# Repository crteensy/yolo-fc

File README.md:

# Yolo FC, STM32F7, 2-6S
This FC has been test flown with a 3" quad, and it flew well. flight logs of the maiden flight are in /logs

- Main MCU: STM32F745
- IMU: ICM-20602
- Flash: 8MB
- Baro: BMP280
- OSD: '7456
- GNSS: Integrated GPS module (uBlox ZOE-M8Q) with u.Fl connector and experimental support for active antennas
- 4 ESCs:
  - EFM8BB21 / bluejay
  - Calculated current rating of 20A continuous 30A burst (depending on the airflow cooling situation)
- Current sensor: INA186 with 0m5 shunt - subjectively some of the best current measurements we have seen on any FC
- 4 multi purpose expansion connectors:
  - each with its own UART
  - shared I2C bus
  - 5V, 3V3 and GND
  - a multi-purpose pin for analog RSSI, Buzzer, LEDs, etc.
- One video expansion connector:
  - Camera in and VTx out
  - UART
  - 2 multi-purpose pins
  - switchable 5V (*)
- size: 30 x 25.2 mm

The expansion connectors can be used with very simple or more complex plug-ins for
- Rx of your choice
- Magnetometer
- Buzzer
- LED strip
- dual camera switching on the OSD connector
- even additional plugin ESCs for hexa- and octocopters are possible

*) The OSD connector has a 5V output that is only ON when USB is not plugged in. This protects your USB port from power hungry VTx'es that might overload the port. However, that feature can be disabled with a solder bridge.

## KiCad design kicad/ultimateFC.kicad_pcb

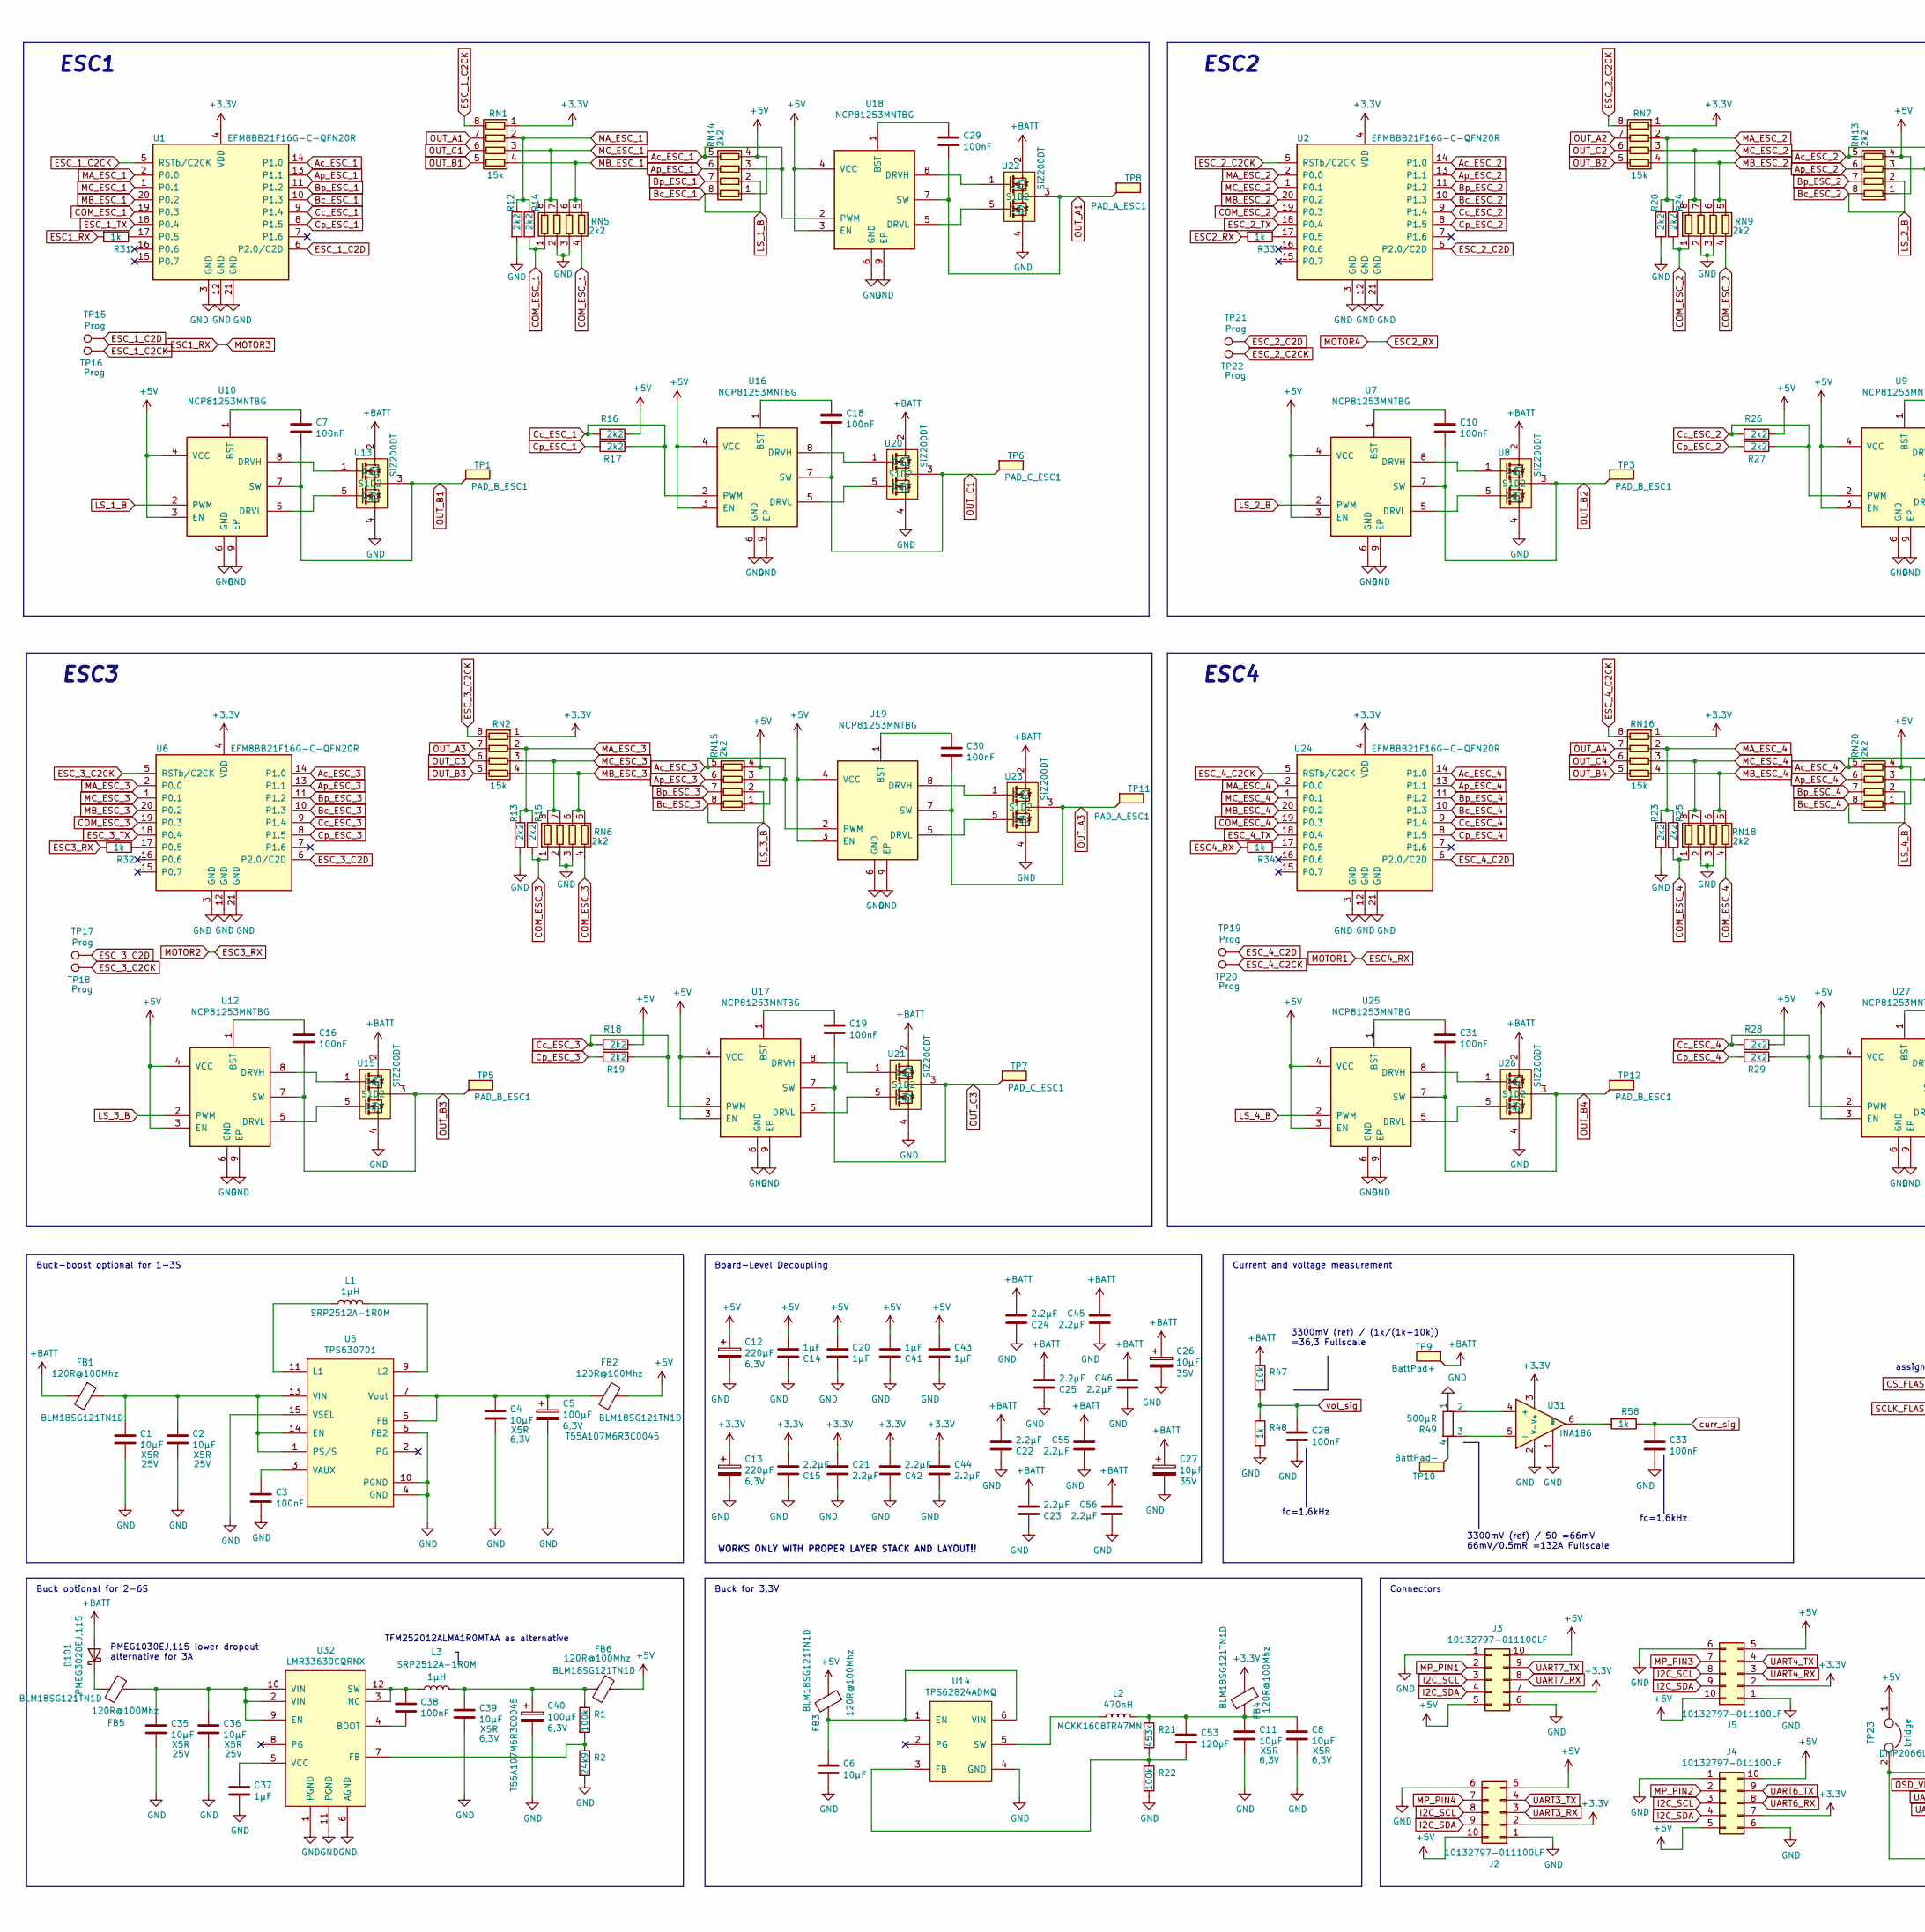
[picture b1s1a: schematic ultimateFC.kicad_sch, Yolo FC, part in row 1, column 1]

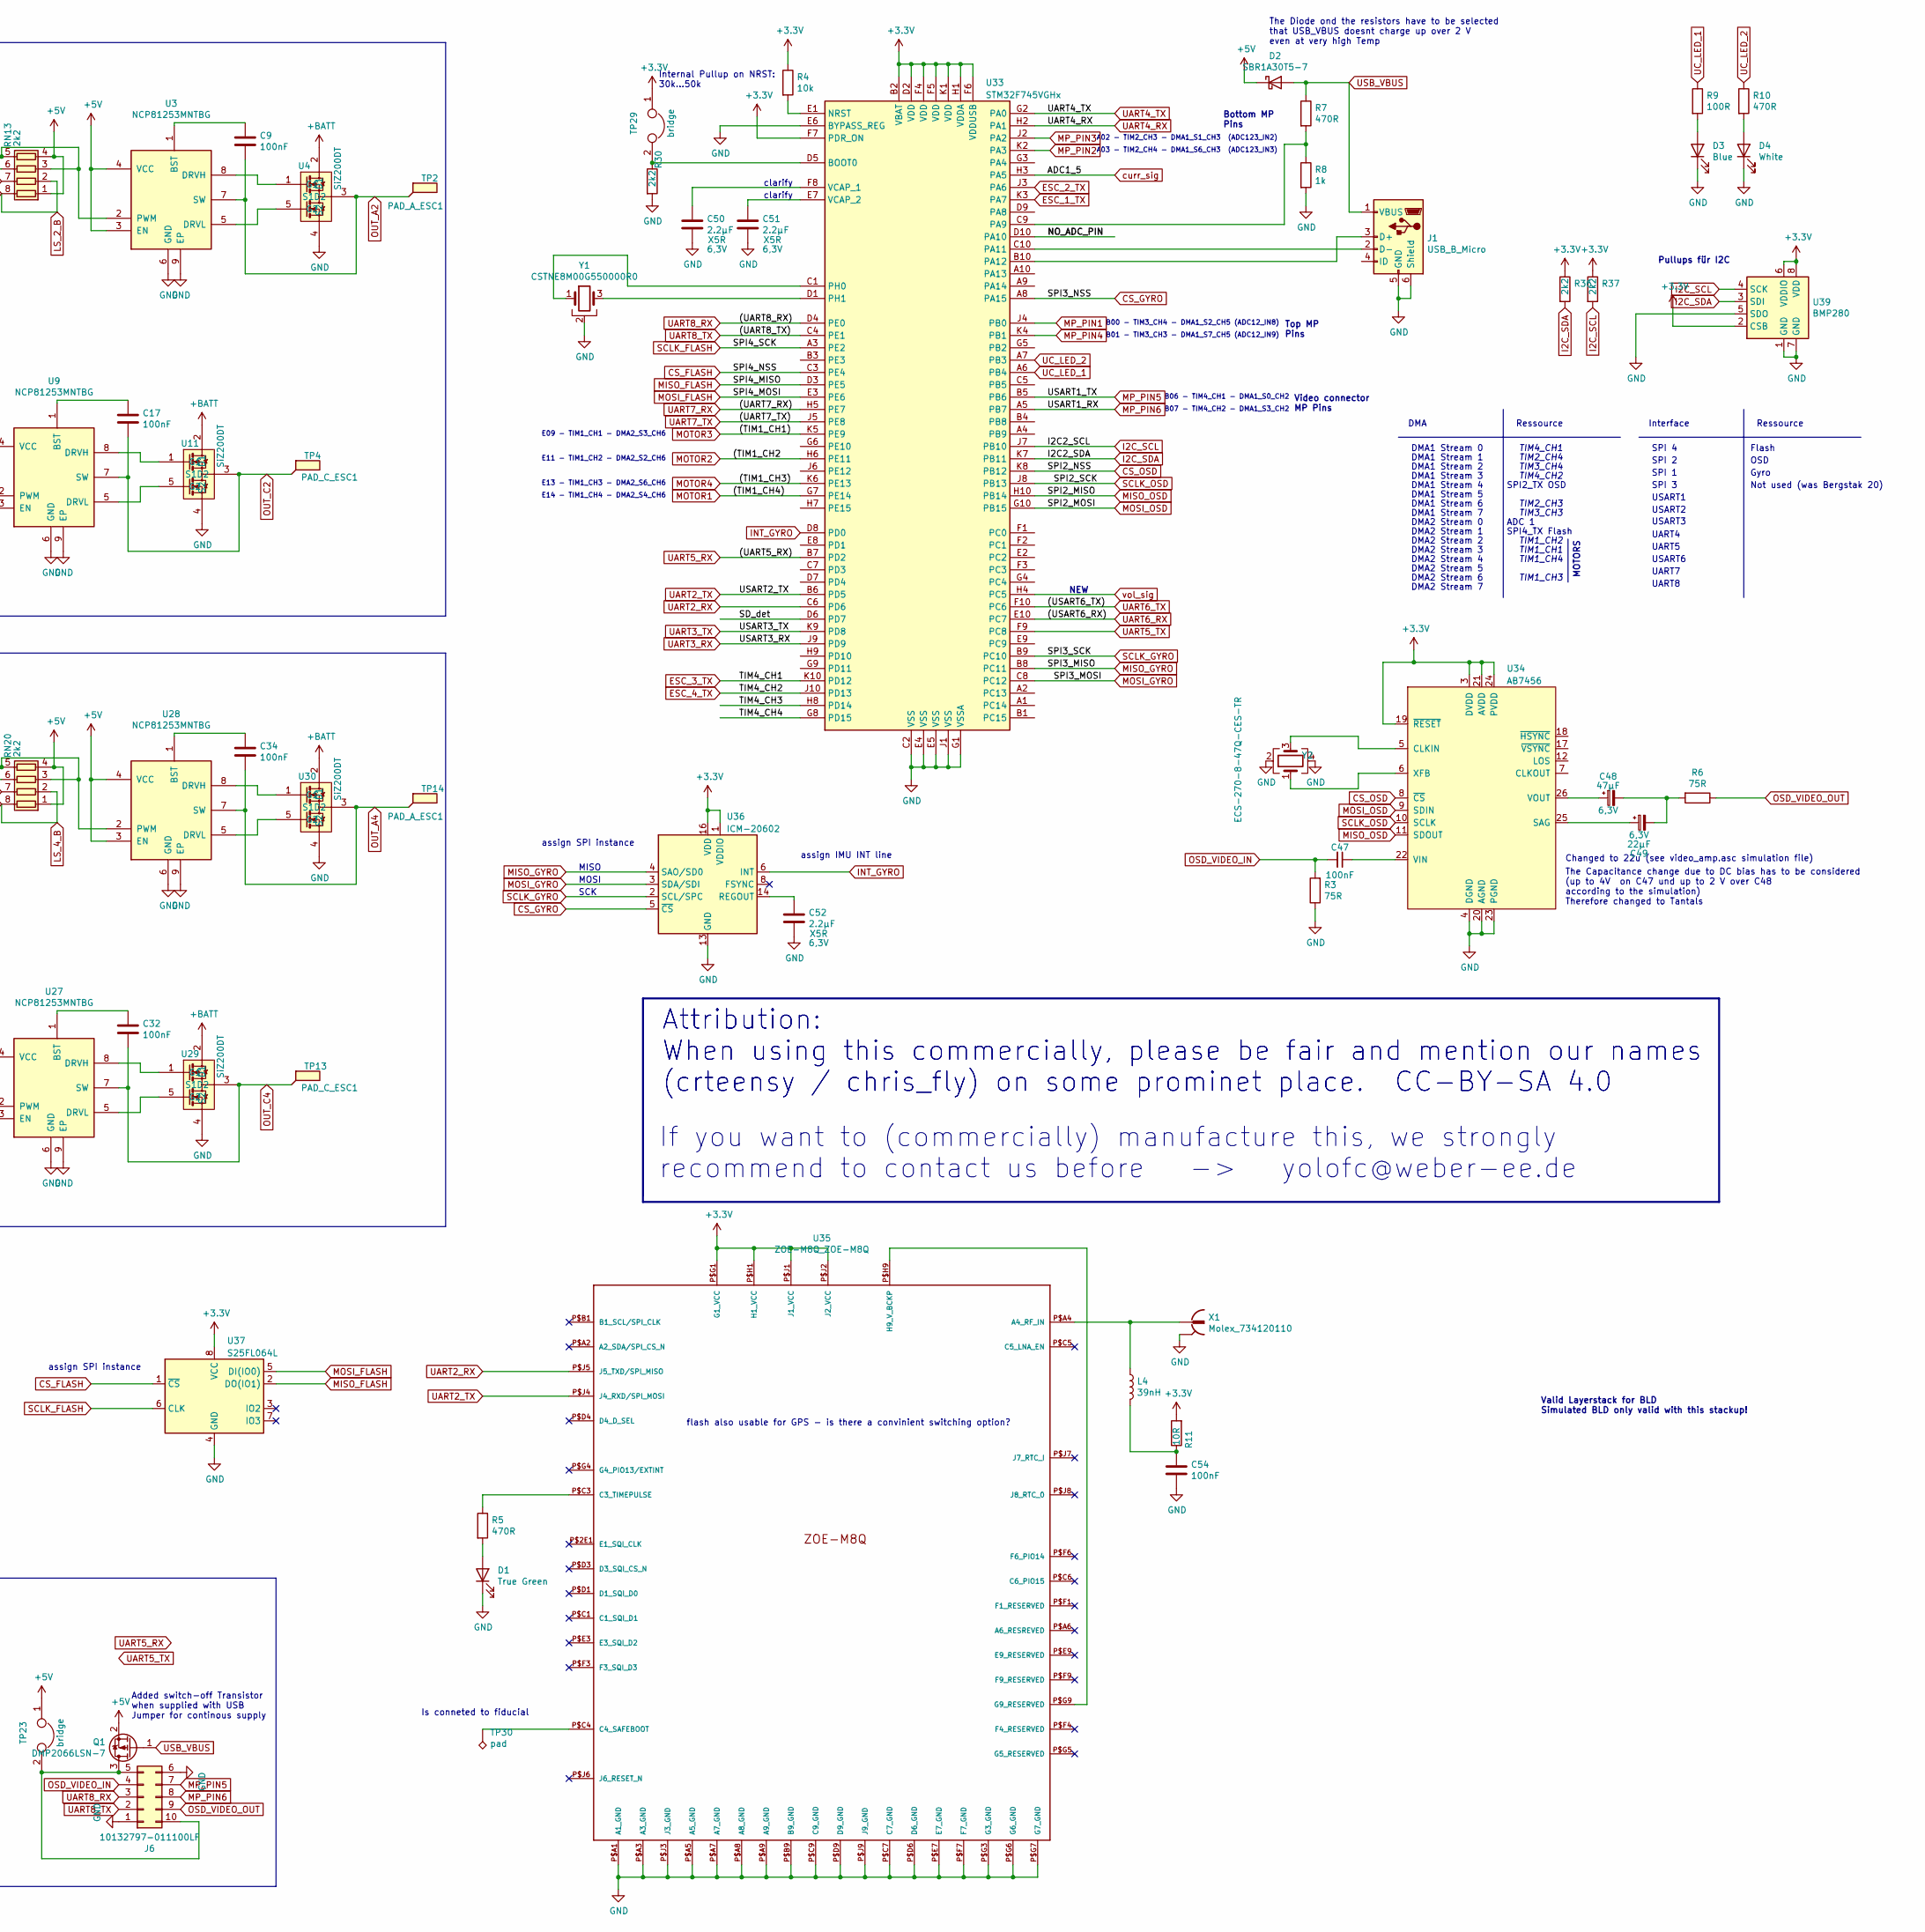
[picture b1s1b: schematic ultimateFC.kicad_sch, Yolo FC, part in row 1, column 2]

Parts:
C1, C2, C35, C36: 10µF; C_1206_3216Metric
C3, C28, C33, C38, C47, C54: 100nF; C_0201_0603Metric_mod
C4, C6, C8, C11, C39: 10µF; C_0603_1608Metric
C5, C40: 100µF; CP_EIA-3216-10_Kemet-I
C7, C9, C10, C16, C17, C18, C19, C29, C30, C31, C32, C34: 100nF; C_0402_1005Metric
C12, C13: 220µF; CP_EIA-3528-15_AVX-H
C14, C20, C41, C43: 1µF; C_AVX_Super_Low_ESL
C15, C21, C42, C44: 2.2µF; C_AVX_Super_Low_ESL
C22, C23, C24, C25, C45, C46, C55, C56: 2.2µF; C_0603_1608Metric
C26, C27: 10µF; CP_EIA-3216-18_Kemet-A
C37: 1µF; C_0402_1005Metric
C48: 47µF; C_0603_1608Metric
C49: 22µF; C_0603_1608Metric
C50, C51, C52: 2.2µF; C_0402_1005Metric
C53: 120pF; C_0201_0603Metric_mod
D1: True Green; LED_0201_0603Metric
D2: SBR1A30T5-7; D_SOD-523
D3: Blue; LED_0201_0603Metric
D4: White; LED_0201_0603Metric
D101: PMEG3020EJ,115; D_SOD-323
FB1, FB2, FB3, FB4, FB5, FB6: 120R@100Mhz; L_0603_1608Metric
J1: USB_B_Micro; USB_Micro-B_Molex_47346-0001
J2, J3, J4, J5, J6: 10132797-011100LF
L1, L3: 1µH; L_Wuerth_MAPI-2506
L2: 470nH; L_0603_1608Metric
L4: 39nH; L_0201_0603Metric
Q1: DMP2066LSN-7; SOT-323_SC-70
R1, R22: 100k; R_0201_0603Metric_mod
R2: 24k9; R_0201_0603Metric_mod
R3, R6: 75R; R_0402_1005Metric
R4: 10k; R_0201_0603Metric_mod
R5, R7, R10: 470R; R_0201_0603Metric_mod
R8, R31, R32, R33, R34, R48, R58: 1k; R_0201_0603Metric_mod
R9: 100R; R_0201_0603Metric_mod
R11: 10R; R_0201_0603Metric_mod
R12, R13, R14, R15, R16, R17, R18, R19, R20, R23, R24, R25, R26, R27, R28, R29, R30, R36, R37: 2k2; R_0201_0603Metric_mod
R21: 453k; R_0201_0603Metric_mod
R47: 10k; R_0402_1005Metric
R49: 500µR; R_Shunt_Vishay_WSKW0612
RN1, RN2, RN7, RN16: 15k; R_Array_Convex_4x0402
RN5, RN6, RN9, RN13, RN14, RN15, RN18, RN20: 2k2; EXB18V_0201x4
TP1, TP3, TP5, TP12: PAD_B_ESC1; esc_pad
TP2, TP8, TP11, TP14: PAD_A_ESC1; esc_pad
TP4, TP6, TP7, TP13: PAD_C_ESC1; esc_pad
TP9: BattPad+; batt_conn_oval
TP10: BattPad-; batt_conn_oval
TP15, TP16, TP17, TP18, TP19, TP20, TP21, TP22: Prog; programm_pad_esc
TP23, TP29: bridge; solderbridge_tiny
TP30: pad; TestPoint_Pad_1.0x1.0mm
U1, U2, U6, U24: EFM8BB21F16G-C-QFN20R; SiliconLabs_QFN-20-1EP_3x3mm_P0.5mm
U3, U7, U9, U10, U12, U16, U17, U18, U19, U25, U27, U28: NCP81253MNTBG; DFN-8-1EP_2x2mm_P0.5mm_EP0.9x1.3mm
U4, U8, U11, U13, U15, U20, U21, U22, U23, U26, U29, U30: SiZ200DT; PowerPAIR3.3x3.3
U5: TPS630701; TEXAS_15-VQFN-HR
U14: TPS62824ADMQ; VSON_HR6
U31: INA186; SOT-363_SC-70-6
U32: LMR33630CQRNX; Texas_RNX0012B
U33: STM32F745VGHx; TFBGA-100_8x8mm_Layout10x10_P0.8mm
U34: AB7456; TSSOP-28_4.4x9.7mm_P0.65mm
U35: ZOE-M8Q_ZOE-M8Q; ZOE-M8
U36: ICM-20602; LGA-16_3x3mm_P0.5mm_LayoutBorder3x5y
U37: S25FL064L; WSON-8_4x4mm_P0.8mm
U39: BMP280; Bosch_LGA-8_2x2.5mm_P0.65mm_ClockwisePinNumbering
X1: Molex_734120110
Y1: CSTNE8M00G550000R0; Resonator_SMD_muRata_CSTxExxV-3Pin_3.0x1.1mm
Y2: ECS-270-8-47Q-CES-TR; ECX-1247Q

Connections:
+3V3: C13.1, C15.2, C21.1, C42.2, C44.1, FB4.1, J2.2, J3.7, J4.7, J5.2, R4.1, R11.2, R36.1, R37.1, RN1.1 (R1.1), RN2.1 (R1.1), RN7.1 (R1.1), RN16.1 (R1.1), TP29.1, U1.4 (VDD), U2.4 (VDD), U6.4 (VDD), U24.4 (VDD), U31.3 (V+), U33.B2 (VBAT), U33.D2 (VDD), U33.F4 (VDD), U33.F5 (VDD), U33.F6 (VDDUSB), U33.F7 (PDR_ON), U33.H1 (VDDA), U33.K1 (VDD), U34.3 (DVDD), U34.19 (~RESET), U34.21 (AVDD), U34.24 (PVDD), U35.P$G1 (G1_VCC), U35.P$H1 (H1_VCC), U35.P$J1 (J1_VCC), U35.P$J2 (J2_VCC), U36.1 (VDDIO), U36.16 (VDD), U37.8 (VCC), U39.2 (CSB), U39.6 (VDDIO), U39.8 (VDD)
+5V: C12.1, C14.2, C20.1, C41.2, C43.1, D2.1 (K), FB2.1, FB3.1, FB6.1, J2.5, J2.10, J3.5, J3.10, J4.5, J4.10, J5.5, J5.10, Q1.2 (S), R16.1, R18.1, R26.1, R28.1, RN13.1 (R1.1), RN13.4 (R4.1), RN14.1 (R1.1), RN14.4 (R4.1), RN15.1 (R1.1), RN15.4 (R4.1), RN20.1 (R1.1), RN20.4 (R4.1), TP23.1, U3.3 (EN), U3.4 (VCC), U7.3 (EN), U7.4 (VCC), U9.3 (EN), U9.4 (VCC), U10.3 (EN), U10.4 (VCC), U12.3 (EN), U12.4 (VCC), U16.3 (EN), U16.4 (VCC), U17.3 (EN), U17.4 (VCC), U18.3 (EN), U18.4 (VCC), U19.3 (EN), U19.4 (VCC), U25.3 (EN), U25.4 (VCC), U27.3 (EN), U27.4 (VCC), U28.3 (EN), U28.4 (VCC)
+BATT: C22.2, C23.2, C24.2, C25.2, C26.1, C27.1, C45.1, C46.1, C55.1, C56.1, D101.2 (A), FB1.2, R47.1, TP9.1, U4.2 (D1), U8.2 (D1), U11.2 (D1), U13.2 (D1), U15.2 (D1), U20.2 (D1), U21.2 (D1), U22.2 (D1), U23.2 (D1), U26.2 (D1), U29.2 (D1), U30.2 (D1)
/NO_ADC_PIN: U33.D10 (PA10)
/SD_det: U33.D6 (PD7)
/TIM4_CH3: U33.H8 (PD14)
/TIM4_CH4: U33.G8 (PD15)
Ac_ESC_1: RN14.3 (R3.1), RN14.5 (R4.2), U1.14 (P1.0), U18.2 (PWM)
Ac_ESC_2: RN13.3 (R3.1), RN13.5 (R4.2), U2.14 (P1.0), U3.2 (PWM)
Ac_ESC_3: RN15.3 (R3.1), RN15.5 (R4.2), U6.14 (P1.0), U19.2 (PWM)
Ac_ESC_4: RN20.3 (R3.1), RN20.5 (R4.2), U24.14 (P1.0), U28.2 (PWM)
Ap_ESC_1: RN14.6 (R3.2), U1.13 (P1.1)
Ap_ESC_2: RN13.6 (R3.2), U2.13 (P1.1)
Ap_ESC_3: RN15.6 (R3.2), U6.13 (P1.1)
Ap_ESC_4: RN20.6 (R3.2), U24.13 (P1.1)
Bc_ESC_1: RN14.2 (R2.1), RN14.8 (R1.2), U1.10 (P1.3), U10.2 (PWM)
Bc_ESC_2: RN13.2 (R2.1), RN13.8 (R1.2), U2.10 (P1.3), U7.2 (PWM)
Bc_ESC_3: RN15.2 (R2.1), RN15.8 (R1.2), U6.10 (P1.3), U12.2 (PWM)
Bc_ESC_4: RN20.2 (R2.1), RN20.8 (R1.2), U24.10 (P1.3), U25.2 (PWM)
Bp_ESC_1: RN14.7 (R2.2), U1.11 (P1.2)
Bp_ESC_2: RN13.7 (R2.2), U2.11 (P1.2)
Bp_ESC_3: RN15.7 (R2.2), U6.11 (P1.2)
Bp_ESC_4: RN20.7 (R2.2), U24.11 (P1.2)
COM_ESC_1: R14.2, RN5.1 (R1.1), RN5.4 (R4.1), U1.19 (P0.3)
COM_ESC_2: R24.2, RN9.1 (R1.1), RN9.4 (R4.1), U2.19 (P0.3)
COM_ESC_3: R15.2, RN6.1 (R1.1), RN6.4 (R4.1), U6.19 (P0.3)
COM_ESC_4: R25.2, RN18.1 (R1.1), RN18.4 (R4.1), U24.19 (P0.3)
CS_FLASH: U33.C3 (PE4), U37.1 (~CS)
CS_GYRO: U33.A8 (PA15), U36.5 (~CS)
CS_OSD: U33.K8 (PB12), U34.8 (~CS)
Cc_ESC_1: R16.2, R17.1, U1.9 (P1.4), U16.2 (PWM)
Cc_ESC_2: R26.2, R27.1, U2.9 (P1.4), U9.2 (PWM)
Cc_ESC_3: R18.2, R19.1, U6.9 (P1.4), U17.2 (PWM)
Cc_ESC_4: R28.2, R29.1, U24.9 (P1.4), U27.2 (PWM)
Cp_ESC_1: R17.2, U1.8 (P1.5)
Cp_ESC_2: R27.2, U2.8 (P1.5)
Cp_ESC_3: R19.2, U6.8 (P1.5)
Cp_ESC_4: R29.2, U24.8 (P1.5)
ESC1_RX: R31.2, U33.K5 (PE9)
ESC2_RX: R33.2, U33.K6 (PE13)
ESC3_RX: R32.2, U33.H6 (PE11)
ESC4_RX: R34.2, U33.G7 (PE14)
ESC_1_C2CK: RN1.8 (R1.2), TP16.1, U1.5 (RSTb/C2CK)
ESC_1_C2D: TP15.1, U1.6 (P2.0/C2D)
ESC_1_TX: U1.18 (P0.4), U33.K3 (PA7)
ESC_2_C2CK: RN7.8 (R1.2), TP22.1, U2.5 (RSTb/C2CK)
ESC_2_C2D: TP21.1, U2.6 (P2.0/C2D)
ESC_2_TX: U2.18 (P0.4), U33.J3 (PA6)
ESC_3_C2CK: RN2.8 (R1.2), TP18.1, U6.5 (RSTb/C2CK)
ESC_3_C2D: TP17.1, U6.6 (P2.0/C2D)
ESC_3_TX: U6.18 (P0.4), U33.K10 (PD12)
ESC_4_C2CK: RN16.8 (R1.2), TP20.1, U24.5 (RSTb/C2CK)
ESC_4_C2D: TP19.1, U24.6 (P2.0/C2D)
ESC_4_TX: U24.18 (P0.4), U33.J10 (PD13)
GND: C1.2, C2.2, C3.2, C4.2, C5.2, C6.2, C8.2, C11.2, C12.2, C13.2, C14.1, C15.1, C20.2, C21.2, C22.1, C23.1, C24.1, C25.1, C26.2, C27.2, C28.2, C33.2, C35.2, C36.2, C37.2, C39.2, C40.2, C41.1, C42.1, C43.2, C44.2, C45.2, C46.2, C50.2, C51.2, C52.2, C54.2, C55.2, C56.2, D1.1 (K), D3.1 (K), D4.1 (K), J1.5 (GND), J1.6 (Shield), J2.1, J2.6, J3.1, J3.6, J4.1, J4.6, J5.1, J5.6, J6.1, J6.6, R2.2, R3.1, R8.2, R12.2, R13.2, R20.2, R22.2, R23.2, R30.2, R48.2, R49.1, RN5.2 (R2.1), RN5.3 (R3.1), RN6.2 (R2.1), RN6.3 (R3.1), RN9.2 (R2.1), RN9.3 (R3.1), RN18.2 (R2.1), RN18.3 (R3.1), U1.3 (GND), U1.12 (GND), U1.21 (GND), U2.3 (GND), U2.12 (GND), U2.21 (GND), U3.6 (GND), U3.9 (EP), U4.4 (S2), U5.4 (GND), U5.6 (FB2), U5.10 (PGND), U5.15 (VSEL), U6.3 (GND), U6.12 (GND), U6.21 (GND), U7.6 (GND), U7.9 (EP), U8.4 (S2), U9.6 (GND), U9.9 (EP), U10.6 (GND), U10.9 (EP), U11.4 (S2), U12.6 (GND), U12.9 (EP), U13.4 (S2), U14.4 (GND), U15.4 (S2), U16.6 (GND)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
I2C_SCL: J2.8, J3.3, J4.3, J5.8, R37.2, U33.J7 (PB10), U39.4 (SCK)
I2C_SDA: J2.9, J3.4, J4.4, J5.9, R36.2, U33.K7 (PB11), U39.3 (SDI)
INT_GYRO: U33.D8 (PD0), U36.6 (INT)
MA_ESC_1: R12.1, R14.1, RN1.2 (R2.1), U1.2 (P0.0)
MA_ESC_2: R20.1, R24.1, RN7.2 (R2.1), U2.2 (P0.0)
MA_ESC_3: R13.1, R15.1, RN2.2 (R2.1), U6.2 (P0.0)
MA_ESC_4: R23.1, R25.1, RN16.2 (R2.1), U24.2 (P0.0)
MB_ESC_1: RN1.4 (R4.1), RN5.5 (R4.2), RN5.6 (R3.2), U1.20 (P0.2)
MB_ESC_2: RN7.4 (R4.1), RN9.5 (R4.2), RN9.6 (R3.2), U2.20 (P0.2)
MB_ESC_3: RN2.4 (R4.1), RN6.5 (R4.2), RN6.6 (R3.2), U6.20 (P0.2)
MB_ESC_4: RN16.4 (R4.1), RN18.5 (R4.2), RN18.6 (R3.2), U24.20 (P0.2)
MC_ESC_1: RN1.3 (R3.1), RN5.7 (R2.2), RN5.8 (R1.2), U1.1 (P0.1)
MC_ESC_2: RN7.3 (R3.1), RN9.7 (R2.2), RN9.8 (R1.2), U2.1 (P0.1)
MC_ESC_3: RN2.3 (R3.1), RN6.7 (R2.2), RN6.8 (R1.2), U6.1 (P0.1)
MC_ESC_4: RN16.3 (R3.1), RN18.7 (R2.2), RN18.8 (R1.2), U24.1 (P0.1)
MISO_FLASH: U33.D3 (PE5), U37.2 (DO(IO1))
MISO_GYRO: U33.B8 (PC11), U36.4 (SAO/SD0)
MISO_OSD: U33.H10 (PB14), U34.11 (SDOUT)
MOSI_FLASH: U33.E3 (PE6), U37.5 (DI(IO0))
MOSI_GYRO: U33.C8 (PC12), U36.3 (SDA/SDI)
MOSI_OSD: U33.G10 (PB15), U34.9 (SDIN)
MP_PIN1: J3.2, U33.J4 (PB0)
MP_PIN2: J4.2, U33.K2 (PA3)
MP_PIN3: J5.7, U33.J2 (PA2)
MP_PIN4: J2.7, U33.K4 (PB1)
MP_PIN5: J6.7, U33.B5 (PB6)
MP_PIN6: J6.8, U33.A5 (PB7)
unnamed: C1.1, C2.1, FB1.1, U5.1 (PS/S), U5.13 (VIN), U5.14 (EN)
unnamed: C3.1, U5.3 (VAUX)
unnamed: C4.1, C5.1, FB2.2, U5.5 (FB), U5.7 (Vout)
unnamed: C6.1, FB3.2, U14.1 (EN), U14.6 (VIN)
unnamed: C7.1, U10.1 (BST)
unnamed: C9.1, U3.1 (BST)
unnamed: C10.1, U7.1 (BST)
unnamed: C8.1, C11.1, C53.1, FB4.2, L2.2, R21.1
unnamed: C16.1, U12.1 (BST)
unnamed: C17.1, U9.1 (BST)
unnamed: C18.1, U16.1 (BST)
unnamed: C19.1, U17.1 (BST)
unnamed: C29.1, U18.1 (BST)
unnamed: C30.1, U19.1 (BST)
unnamed: C31.1, U25.1 (BST)
unnamed: C32.1, U27.1 (BST)
unnamed: C34.1, U28.1 (BST)
unnamed: C35.1, C36.1, FB5.2, U32.2 (VIN), U32.9 (EN), U32.10 (VIN)
unnamed: C37.1, U32.5 (VCC)
unnamed: C38.1, L3.1, U32.3 (NC), U32.12 (SW)
unnamed: C38.2, U32.4 (BOOT)
unnamed: C39.1, C40.1, FB6.2, L3.2, R1.1
unnamed: C47.1, U34.22 (VIN)
unnamed: C48.1, U34.26 (VOUT)
unnamed: C48.2, C49.2, R6.2
unnamed: C49.1, U34.25 (SAG)
unnamed: C50.1, U33.F8 (VCAP_1)
unnamed: C51.1, U33.E7 (VCAP_2)
unnamed: C52.1, U36.14 (REGOUT)
unnamed: C53.2, R21.2, R22.1, U14.3 (FB)
unnamed: C54.1, L4.2, R11.1
unnamed: D1.2 (A), R5.2
unnamed: D3.2 (A), R9.2
unnamed: D4.2 (A), R10.2
unnamed: D101.1 (K), FB5.1
unnamed: J1.2 (D-), U33.C10 (PA11)
unnamed: J1.3 (D+), U33.B10 (PA12)
unnamed: J6.5, J6.10, Q1.3 (D), TP23.2
unnamed: L1.1, U5.11 (L1)
unnamed: L1.2, U5.9 (L2)
unnamed: L2.1, U14.5 (SW)
unnamed: L4.1, U35.P$A4 (A4_RF_IN), X1.1
unnamed: R1.2, R2.1, U32.7 (FB)
unnamed: R4.2, U33.E1 (NRST)
unnamed: R5.1, U35.P$C3 (C3_TIMEPULSE)
unnamed: R7.2, R8.1, U33.C9 (PA9)
unnamed: R30.1, TP29.2, U33.D5 (BOOT0)
unnamed: R31.1, U1.17 (P0.5)
unnamed: R32.1, U6.17 (P0.5)
unnamed: R33.1, U2.17 (P0.5)
unnamed: R34.1, U24.17 (P0.5)
unnamed: R49.2, U31.4 (+)
unnamed: R49.3, U31.5 (-)
unnamed: R49.4, TP10.1
unnamed: R58.2, U31.6
unnamed: TP30.1, U35.P$C4 (C4_SAFEBOOT)
unnamed: U3.5 (DRVL), U4.5 (G2)
unnamed: U3.8 (DRVH), U4.1 (G1)
unnamed: U7.5 (DRVL), U8.5 (G2)
unnamed: U7.8 (DRVH), U8.1 (G1)
unnamed: U10.5 (DRVL), U13.5 (G2)
unnamed: U10.8 (DRVH), U13.1 (G1)
unnamed: U9.8 (DRVH), U11.1 (G1)
unnamed: U9.5 (DRVL), U11.5 (G2)
unnamed: U12.5 (DRVL), U15.5 (G2)
unnamed: U12.8 (DRVH), U15.1 (G1)
unnamed: U16.5 (DRVL), U20.5 (G2)
unnamed: U16.8 (DRVH), U20.1 (G1)
unnamed: U17.5 (DRVL), U21.5 (G2)
unnamed: U17.8 (DRVH), U21.1 (G1)
unnamed: U18.5 (DRVL), U22.5 (G2)
unnamed: U18.8 (DRVH), U22.1 (G1)
unnamed: U19.5 (DRVL), U23.5 (G2)
unnamed: U19.8 (DRVH), U23.1 (G1)
unnamed: U25.5 (DRVL), U26.5 (G2)
unnamed: U25.8 (DRVH), U26.1 (G1)
unnamed: U27.5 (DRVL), U29.5 (G2)
unnamed: U27.8 (DRVH), U29.1 (G1)
unnamed: U28.5 (DRVL), U30.5 (G2)
unnamed: U28.8 (DRVH), U30.1 (G1)
unnamed: U33.C1 (PH0), Y1.1
unnamed: U33.D1 (PH1), Y1.3
unnamed: U34.5 (CLKIN), Y2.3
unnamed: U34.6 (XFB), Y2.1
unnamed: U35.P$G9 (G9_RESERVED), U35.P$H9 (H9_V_BCKP)
OSD_VIDEO_IN: C47.2, J6.4, R3.2
OSD_VIDEO_OUT: J6.9, R6.1
OUT_A1: C29.2, RN1.7 (R2.2), TP8.1, U18.7 (SW), U22.3 (S1D2)
OUT_A2: C9.2, RN7.7 (R2.2), TP2.1, U3.7 (SW), U4.3 (S1D2)
OUT_A3: C30.2, RN2.7 (R2.2), TP11.1, U19.7 (SW), U23.3 (S1D2)
OUT_A4: C34.2, RN16.7 (R2.2), TP14.1, U28.7 (SW), U30.3 (S1D2)
OUT_B1: C7.2, RN1.5 (R4.2), TP1.1, U10.7 (SW), U13.3 (S1D2)
OUT_B2: C10.2, RN7.5 (R4.2), TP3.1, U7.7 (SW), U8.3 (S1D2)
OUT_B3: C16.2, RN2.5 (R4.2), TP5.1, U12.7 (SW), U15.3 (S1D2)
OUT_B4: C31.2, RN16.5 (R4.2), TP12.1, U25.7 (SW), U26.3 (S1D2)
OUT_C1: C18.2, RN1.6 (R3.2), TP6.1, U16.7 (SW), U20.3 (S1D2)
OUT_C2: C17.2, RN7.6 (R3.2), TP4.1, U9.7 (SW), U11.3 (S1D2)
OUT_C3: C19.2, RN2.6 (R3.2), TP7.1, U17.7 (SW), U21.3 (S1D2)
OUT_C4: C32.2, RN16.6 (R3.2), TP13.1, U27.7 (SW), U29.3 (S1D2)
SCLK_FLASH: U33.A3 (PE2), U37.6 (CLK)
SCLK_GYRO: U33.B9 (PC10), U36.2 (SCL/SPC)
SCLK_OSD: U33.J8 (PB13), U34.10 (SCLK)
UART2_RX: U33.C6 (PD6), U35.P$J5 (J5_TXD/SPI_MISO)
UART2_TX: U33.B6 (PD5), U35.P$J4 (J4_RXD/SPI_MOSI)
UART3_RX: J2.3, U33.J9 (PD9)
UART3_TX: J2.4, U33.K9 (PD8)
UART4_RX: J5.3, U33.H2 (PA1)
UART4_TX: J5.4, U33.G2 (PA0)
UART5_RX: U33.B7 (PD2)
UART5_TX: U33.F9 (PC8)
UART6_RX: J4.8, U33.E10 (PC7)
UART6_TX: J4.9, U33.F10 (PC6)
UART7_RX: J3.8, U33.H5 (PE7)
UART7_TX: J3.9, U33.J5 (PE8)
UART8_RX: J6.3, U33.D4 (PE0)
UART8_TX: J6.2, U33.C4 (PE1)
UC_LED_1: R9.1, U33.A6 (PB4)
UC_LED_2: R10.1, U33.A7 (PB3)
USB_VBUS: D2.2 (A), J1.1 (VBUS), Q1.1 (G), R7.1
curr_sig: C33.1, R58.1, U33.H3 (PA5)
vol_sig: C28.1, R47.2, R48.1, U33.H4 (PC5)

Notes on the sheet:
Added switch-off Transistor when supplied with USB Jumper for continous supply
E14 - TIM1_CH4 - DMA2_S4_CH6
The Capacitance change due to DC bias has to be considered (up to 4V on C47 und up to 2 V over C48 according to the simulation) Therefore changed to Tantals
3300mV (ref) / 50 =66mV 66mV/0.5mR =132A Fullscale
Internal Pullup on NRST: 30k...50k
MOTORS
clarify
DMA1 Stream 3
DMA1 Stream 4
Video connector MP Pins
ESC3
UART8
DMA1 Stream 6
SPI 1
TIM4_CH1
E09 - TIM1_CH1 - DMA2_S3_CH6
SCK
TIM1_CH4
DMA2 Stream 2
TIM2_CH4
WORKS ONLY WITH PROPER LAYER STACK AND LAYOUT!!
Bottom MP Pins
ESC2
MOSI
Ressource
assign SPI instance
DMA2 Stream 1
ADC 1
fc=1,6kHz
Gyro
UART4
USART3
B06 - TIM4_CH1 - DMA1_S0_CH2
E11 - TIM1_CH2 - DMA2_S2_CH6
E13 - TIM1_CH3 - DMA2_S6_CH6
DMA2 Stream 6
ESC1
PMEG1030EJ,115 lower dropout alternative for 3A
TIM1_CH1
Buck-boost optional for 1-3S

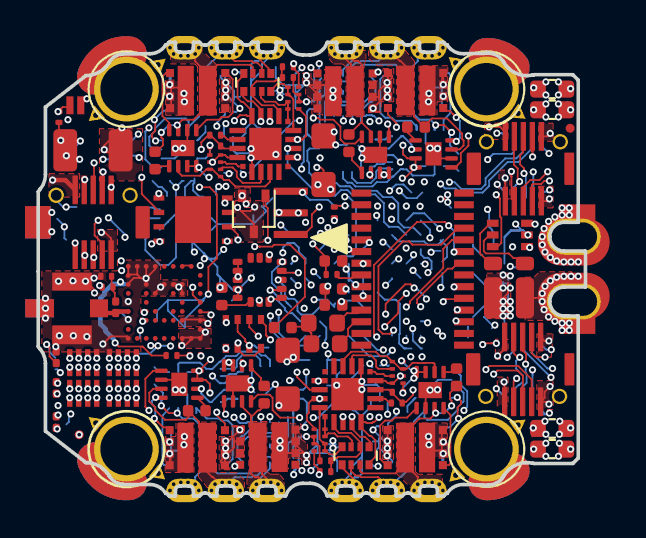
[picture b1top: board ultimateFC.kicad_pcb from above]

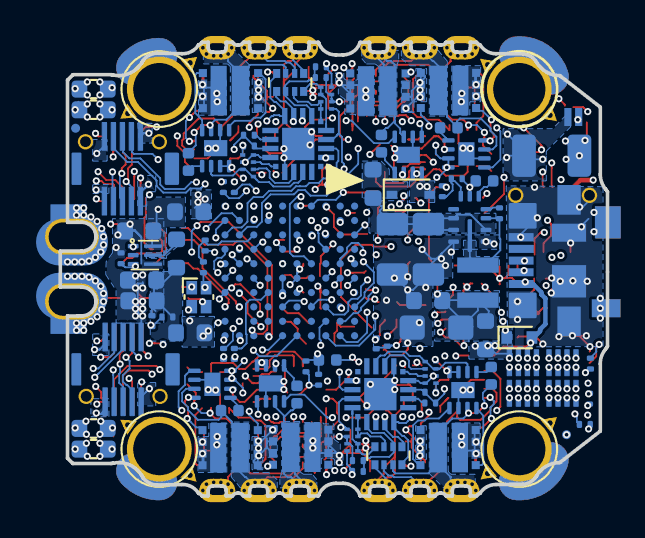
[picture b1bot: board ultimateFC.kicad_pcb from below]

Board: 8 copper layers, 30.4 x 25.2 mm, 186 parts (94 on the bottom side), 191 nets.

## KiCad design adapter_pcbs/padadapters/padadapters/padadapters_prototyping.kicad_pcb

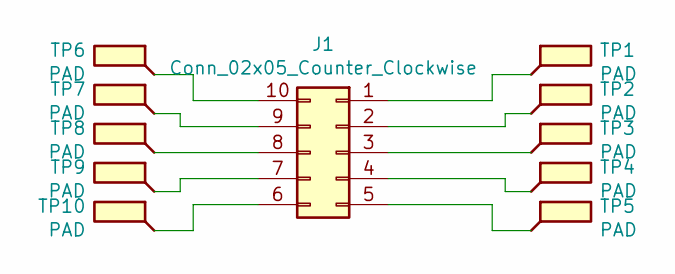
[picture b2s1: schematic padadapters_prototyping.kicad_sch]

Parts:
J1: Conn_02x05_Counter_Clockwise; 10132797-011100LF_mod_small_adapter_pads
TP1, TP2, TP3, TP4, TP5, TP6, TP7, TP8, TP9, TP10: PAD; TestPoint_Pad_1.2x2.5mm

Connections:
unnamed: J1.1, TP1.1
unnamed: J1.2, TP2.1
unnamed: J1.4, TP4.1
unnamed: J1.5, TP5.1
unnamed: J1.6, TP10.1
unnamed: J1.7, TP9.1
unnamed: J1.8, TP8.1
unnamed: J1.9, TP7.1
unnamed: J1.10, TP6.1
unnamed: J1.3, TP3.1

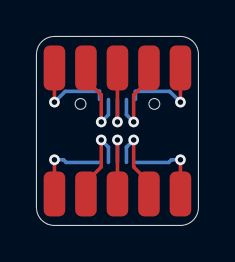
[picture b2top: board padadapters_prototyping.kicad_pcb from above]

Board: 2 copper layers, 9.0 x 10.5 mm, 11 parts (1 on the bottom side), 10 nets.

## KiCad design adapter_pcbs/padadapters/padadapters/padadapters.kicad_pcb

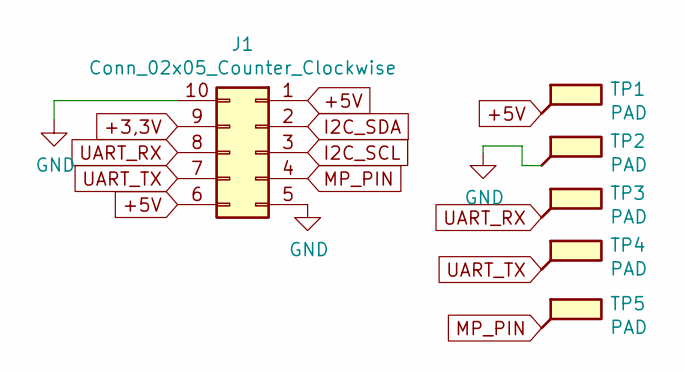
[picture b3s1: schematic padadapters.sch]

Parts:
J1: Conn_02x05_Counter_Clockwise; 10132797-011100LF_mod_small_adapter_pads
TP1, TP2, TP3, TP4, TP5: PAD; TestPoint_Pad_1.2x2.5mm

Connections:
+3,3V: J1.9
+5V: J1.1, J1.6, TP1.1
GND: J1.5, J1.10, TP2.1
I2C_SCL: J1.3
I2C_SDA: J1.2
MP_PIN: J1.4, TP5.1
UART_RX: J1.8, TP3.1
UART_TX: J1.7, TP4.1

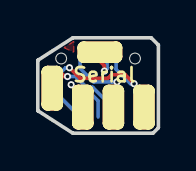
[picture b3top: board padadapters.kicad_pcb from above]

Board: 2 copper layers, 6.7 x 5.3 mm, 6 parts (1 on the bottom side), 5 nets.

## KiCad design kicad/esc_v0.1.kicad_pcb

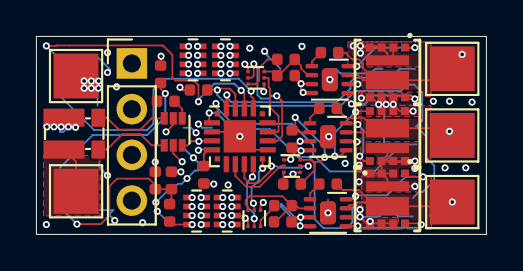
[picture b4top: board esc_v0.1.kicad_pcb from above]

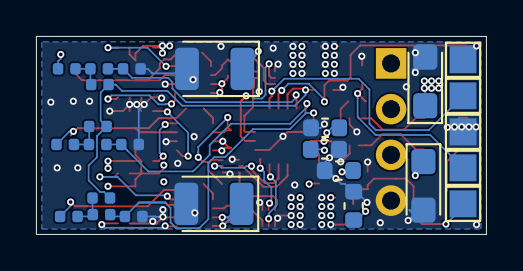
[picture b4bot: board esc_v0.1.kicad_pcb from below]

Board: 8 copper layers, 25.0 x 11.0 mm, 63 parts (25 on the bottom side), 44 nets.

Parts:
C10, C19, C28, C32, C33: 100nF; C_0402_1005Metric
C12, C13: 220µF; CP_EIA-3528-15_AVX-H
C14, C15, C20, C21: 1µF; C_AVX_Super_Low_ESL
C22, C23, C24, C25: 10µF; C_0603_1608Metric
C26, C27: 10µF; CP_EIA-3216-18_Kemet-A
J1: Conn_01x04_Male; PinHeader_1x04_P2.54mm_Vertical
Q10, Q11, Q12: DMN2990UDJ-7; SOT-963
R4, R11, R12, R20, R29, R30, R34, R45, R46, R48, R58, R62, R66: 1k; R_0402_1005Metric
R16, R53, R61, R63, R65, R67: 10k; R_0402_1005Metric
R38, R57, R64: 0; R_0402_1005Metric
R47: 18k; R_0402_1005Metric
R49: 500µR; R_Shunt_Vishay_WSKW0612
TP4: PAD_A_ESC4; TestPoint_Pad_2.5x2.5mm
TP8: PAD_B_ESC4; TestPoint_Pad_2.5x2.5mm
TP9: BattPad+; TestPoint_Pad_2.5x2.5mm
TP10: BattPad-; TestPoint_Pad_2.5x2.5mm
TP14: PAD_C_ESC4; TestPoint_Pad_2.5x2.5mm
TP15, TP16, TP17, TP18, TP19: PAD_C_ESC4; TestPoint_Pad_1.5x1.5mm
U4: EFM8BB21F16G-C-QFN20R; SiliconLabs_QFN-20-1EP_3x3mm_P0.5mm
U9, U18, U26: NCP81253MNTBG; DFN-8-1EP_2x2mm_P0.5mm_EP0.9x1.3mm
U13, U22, U30: SIZ322DT-T1-GE3; PowerPAIR3x3
U31: INA185A2IDRLR; SOT-563

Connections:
+3V3: C13.1, C15.1, C21.1, J1.3, R4.1, U4.4, U31.6
+5V: C12.1, C14.1, C20.1, J1.2, R11.1, R29.1, R45.1, U9.3, U9.4, U18.3, U18.4, U26.3, U26.4
+BATT: C22.1, C23.1, C24.1, C25.1, C26.1, C27.1, J1.1, R47.1, TP9.1, U13.2, U22.2, U30.2
Ac_ESC_4: Q10.2, U4.13
Ap_ESC_4: Q10.5, U4.14
Bc_ESC_4: Q11.2, U4.10
Bp_ESC_4: Q11.5, U4.11
COM_ESC_4: R34.1, R53.1, R63.1, R67.1, U4.19
Cc_ESC_4: Q12.2, U4.8
Cp_ESC_4: Q12.5, U4.9
ESC4_RX: TP17.1, U4.17
ESC_4_C2CK: R4.2, U4.5
ESC_4_TX: TP18.1, U4.18
GND: C12.2, C13.2, C14.2, C15.2, C20.2, C21.2, C22.2, C23.2, C24.2, C25.2, C26.2, C27.2, C28.2, C33.2, J1.4, Q10.1, Q10.4, Q11.1, Q11.4, Q12.1, Q12.4, R20.1, R34.2, R48.2, R49.1, R62.1, R66.1, TP19.1, U4.3, U4.12, U4.21, U9.6, U9.9, U13.4, U18.6, U18.9, U22.4, U26.6, U26.9, U30.4, U31.2, U31.5
MA_ESC_4: R16.2, R20.2, U4.20
MB_ESC_4: R61.2, R62.2, U4.2
MC_ESC_4: R65.2, R66.2, U4.1
unnamed: C10.1, U9.1
unnamed: C10.2, R38.1, TP4.1, U9.7, U13.3
unnamed: C19.1, U18.1
unnamed: C19.2, R57.1, TP8.1, U18.7, U22.3
unnamed: C32.1, U26.1
unnamed: C32.2, R64.1, TP14.1, U26.7, U30.3
unnamed: Q10.3, R12.2
unnamed: Q10.6, R11.2, R12.1, U9.2
unnamed: Q11.3, R30.2
unnamed: Q11.6, R29.2, R30.1, U18.2
unnamed: Q12.3, R46.2
unnamed: Q12.6, R45.2, R46.1, U26.2
unnamed: R16.1, R38.2, R53.2
unnamed: R49.2, U31.3
unnamed: R49.3, U31.4
unnamed: R49.4, TP10.1
unnamed: R57.2, R61.1, R63.2
unnamed: R58.2, U31.1
unnamed: R64.2, R65.1, R67.2
unnamed: U9.8, U13.1
unnamed: U9.5, U13.5
unnamed: U18.5, U22.5
unnamed: U18.8, U22.1
unnamed: U26.5, U30.5
unnamed: U26.8, U30.1
curr_sig: C33.1, R58.1, TP15.1
vol_sig: C28.1, R47.2, R48.1, TP16.1

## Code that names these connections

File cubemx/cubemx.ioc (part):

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Mcu.Name=STM32F745V(E-G)Hx
Mcu.Package=TFBGA100
Mcu.UserName=STM32F745VGHx
PA0/WKUP.Mode=Asynchronous
PA0/WKUP.Signal=UART4_TX
PA1.Mode=Asynchronous
PA1.Signal=UART4_RX
PA11.Mode=Device_Only
PA11.Signal=USB_OTG_FS_DM
PA12.Mode=Device_Only
PA12.Signal=USB_OTG_FS_DP
PA15.Signal=SPI3_NSS
PA2.Signal=S_TIM2_CH3
PA3.Signal=S_TIM2_CH4
PA5.Signal=ADCx_IN5
PA6.Signal=S_TIM3_CH1
PA7.Signal=S_TIM3_CH2
PA9.Mode=Activate_VBUS
PA9.Signal=USB_OTG_FS_VBUS
PB0.Signal=S_TIM3_CH3
PB1.Signal=S_TIM3_CH4
PB10.Mode=I2C
PB10.Signal=I2C2_SCL
PB11.Mode=I2C
PB11.Signal=I2C2_SDA
PB12.Signal=SPI2_NSS
PB13.Mode=Full_Duplex_Master
PB13.Signal=SPI2_SCK
PB14.Mode=Full_Duplex_Master
PB14.Signal=SPI2_MISO
PB15.Mode=Full_Duplex_Master
PB15.Signal=SPI2_MOSI
PB3.Signal=GPIO_Output
PB4.Signal=GPIO_Output
PB6.Mode=Asynchronous
PB6.Signal=USART1_TX
PB7.Mode=Asynchronous
PB7.Signal=USART1_RX
PC10.Mode=Full_Duplex_Master
PC10.Signal=SPI3_SCK
PC11.Mode=Full_Duplex_Master
PC11.Signal=SPI3_MISO
PC12.Mode=Full_Duplex_Master
PC12.Signal=SPI3_MOSI
PC5.Signal=ADCx_IN15
PC6.Mode=Asynchronous
PC6.Signal=USART6_TX
PC7.Mode=Asynchronous
PC7.Signal=USART6_RX
PD0.Signal=GPIO_Input
PD12.Signal=S_TIM4_CH1
PD13.Signal=S_TIM4_CH2
PD2.Signal=UART5_RX
PD5.Mode=Asynchronous
PD5.Signal=USART2_TX
PD6.Mode=Asynchronous
PD6.Signal=USART2_RX
PD7.Signal=GPIO_Input
PD8.Mode=Asynchronous
PD8.Signal=USART3_TX
PD9.Mode=Asynchronous
PD9.Signal=USART3_RX
PE0.Mode=Asynchronous
PE0.Signal=UART8_RX
PE1.Mode=Asynchronous
PE1.Signal=UART8_TX
PE11.Signal=S_TIM1_CH2
PE13.Signal=S_TIM1_CH3
PE14.Signal=S_TIM1_CH4
PE2.Mode=Full_Duplex_Master
PE2.Signal=SPI4_SCK
PE4.Signal=SPI4_NSS
PE5.Mode=Full_Duplex_Master
PE5.Signal=SPI4_MISO
PE6.Mode=Full_Duplex_Master
PE6.Signal=SPI4_MOSI
PE7.Mode=Asynchronous
PE7.Signal=UART7_RX
PE8.Mode=Asynchronous
PE8.Signal=UART7_TX
PE9.Signal=S_TIM1_CH1
PH0/OSC_IN.Mode=HSE-External-Oscillator
PH0/OSC_IN.Signal=RCC_OSC_IN
PH1/OSC_OUT.Mode=HSE-External-Oscillator
PH1/OSC_OUT.Signal=RCC_OSC_OUT
RCC.HSE_VALUE=25000000
board=custom

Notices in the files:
kicad/ultimateFC.kicad_sch:
(crteensy / chris_fly) on some prominet place.  CC-BY-SA 4.0
